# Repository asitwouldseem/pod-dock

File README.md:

# pod-dock
A modern docking station for fruit branded MP3 players.

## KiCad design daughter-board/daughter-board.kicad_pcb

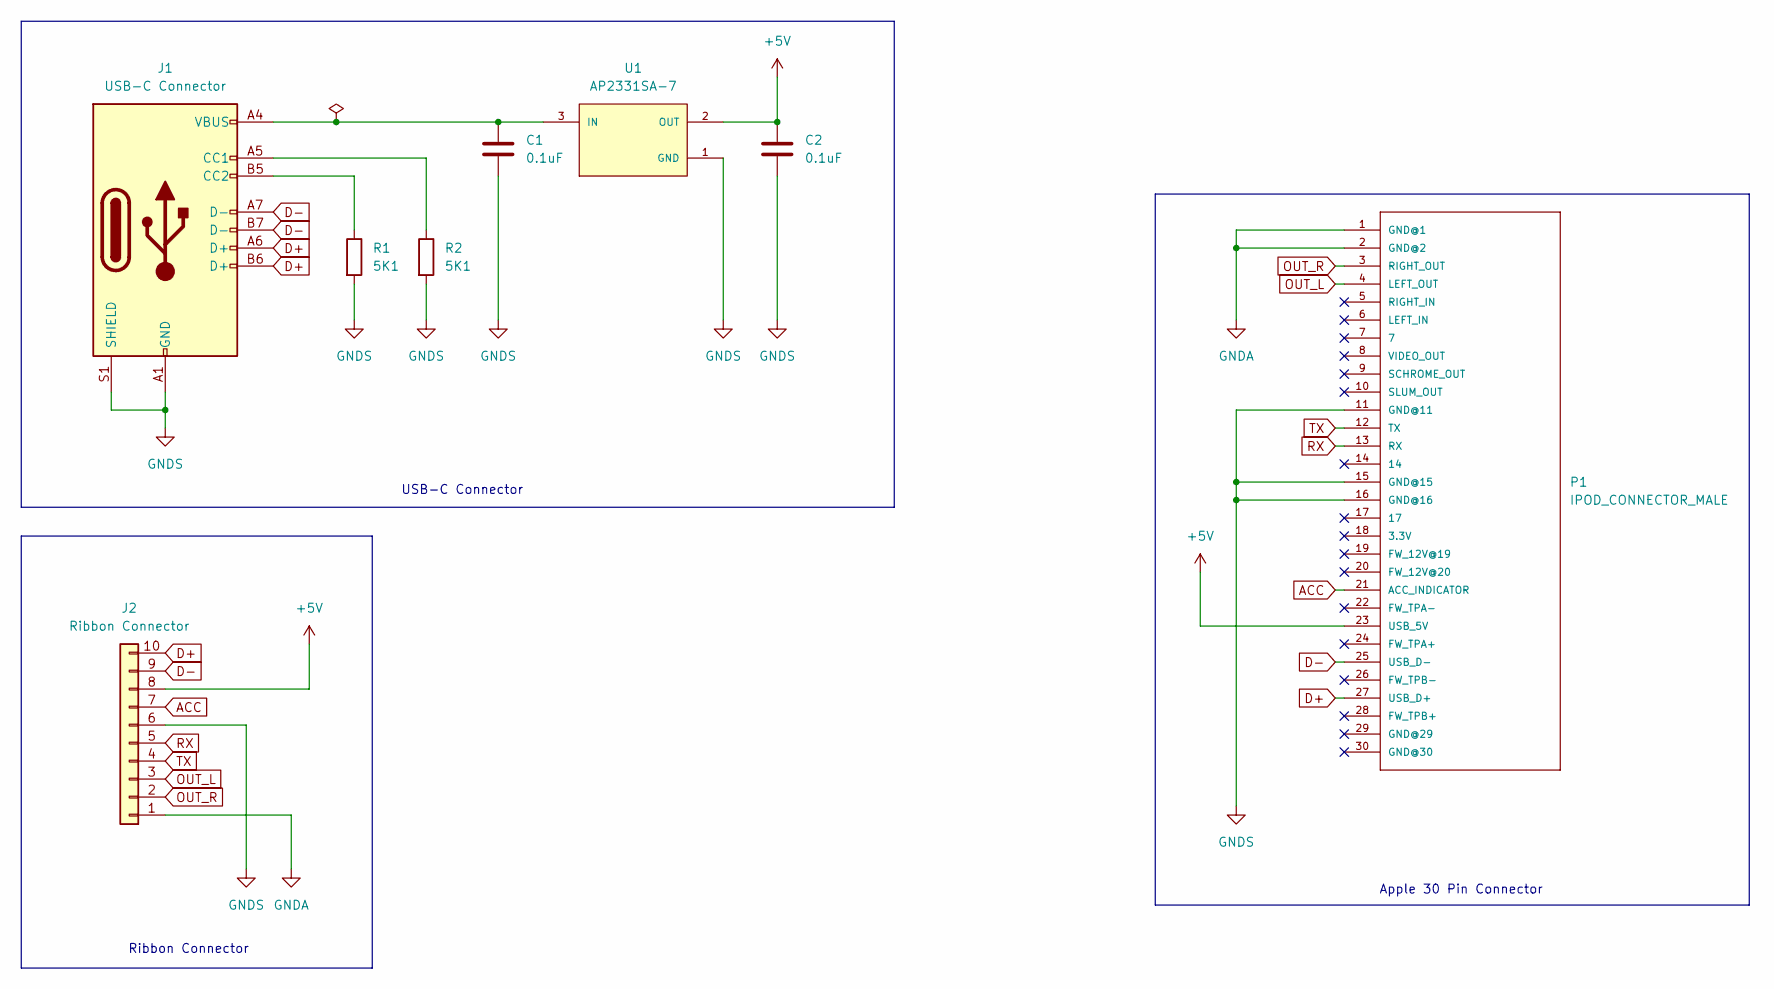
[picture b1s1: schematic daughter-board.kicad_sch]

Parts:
C1, C2: 0.1uF; C_0805_2012Metric_Pad1.18x1.45mm_HandSolder
J1: USB-C Connector; USB_C_Receptacle_HRO_TYPE-C-31-M-12
J2: Ribbon Connector; Molex_54548-1071_1x10-1MP_P0.5mm_Horizontal
P1: IPOD_CONNECTOR_MALE; ipod-connector_male
R1, R2: 5K1; R_0805_2012Metric_Pad1.20x1.40mm_HandSolder
U1: AP2331SA-7; SOT91P240X120-3N

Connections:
+5V: C2.1, J2.8, P1.23 (USB_5V), U1.2 (OUT)
ACC: J2.7, P1.21 (ACC_INDICATOR)
D+: J1.A6 (D+), J1.B6 (D+), J2.10, P1.27 (USB_D+)
D-: J1.A7 (D-), J1.B7 (D-), J2.9, P1.25 (USB_D-)
GNDA: J2.1, P1.1 (GND@1), P1.2 (GND@2)
GNDS: C1.2, C2.2, J1.A1 (GND), J1.A12 (GND), J1.B1 (GND), J1.B12 (GND), J1.S1 (SHIELD), J2.6, P1.11 (GND@11), P1.15 (GND@15), P1.16 (GND@16), R1.2, R2.2, U1.1 (GND)
unnamed: J1.A5 (CC1), R2.1
unnamed: J1.B5 (CC2), R1.1
unnamed: C1.1, J1.A4 (VBUS), J1.A9 (VBUS), J1.B4 (VBUS), J1.B9 (VBUS), U1.3 (IN)
OUT_L: J2.3, P1.4 (LEFT_OUT)
OUT_R: J2.2, P1.3 (RIGHT_OUT)
RX: J2.5, P1.13 (RX)
TX: J2.4, P1.12 (TX)

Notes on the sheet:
Apple 30 Pin Connector
Ribbon Connector
USB-C Connector

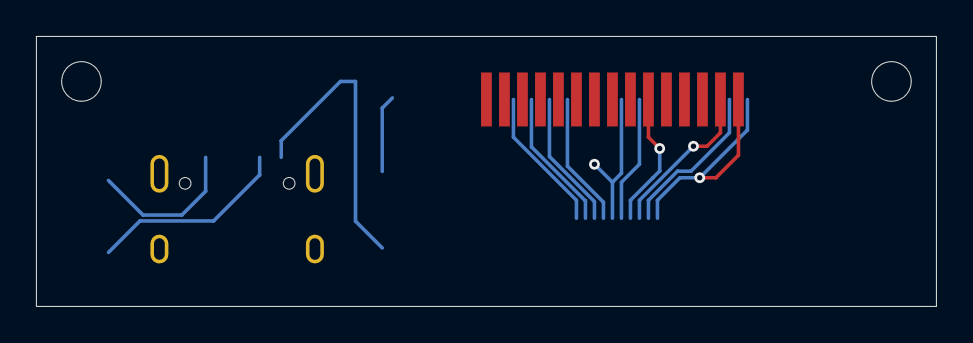
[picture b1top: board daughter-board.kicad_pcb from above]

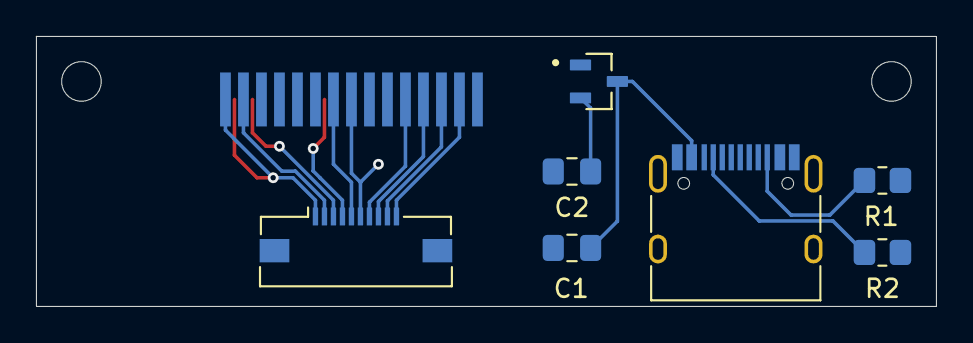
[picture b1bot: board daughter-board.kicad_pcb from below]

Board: 2 copper layers, 50.0 x 15.0 mm, 8 parts (7 on the bottom side), 13 nets.

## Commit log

2026-01-20 Init project
2026-01-20 Add P1 + 500K resistor for serial
2026-01-20 Add charging connections
2026-01-20 Add USB-C
2026-01-25 Split project into two boards
2026-01-25 Change FFC to match fab house.
2026-01-25 FFC routing
2026-01-25 Eh, not sure about this.
2026-01-30 Add TSOP module
